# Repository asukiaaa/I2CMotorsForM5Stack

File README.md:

# I2cMotorsForM5Stack

A motor driver with using atmega328p for M5Stack.

# Components

- [TB6612FNG](http://akizukidenshi.com/catalog/g/gI-11317/)
- [Diode](https://akizukidenshi.com/catalog/g/gI-02073/)
- [Terminal block](https://akizukidenshi.com/catalog/g/gP-08370/)
- Gear motor 6v200rpm

# License

MIT

# References

- [SparkFun Motor Driver - Dual TB6612FNG (1A)](https://www.sparkfun.com/products/14451)
- [CavityForM5Stack](https://github.com/asukiaaa/CavityForM5Stack)
- [Arduino Pro Mini schematic (PDF)](https://www.arduino.cc/en/uploads/Main/Arduino-Pro-Mini-schematic.pdf)

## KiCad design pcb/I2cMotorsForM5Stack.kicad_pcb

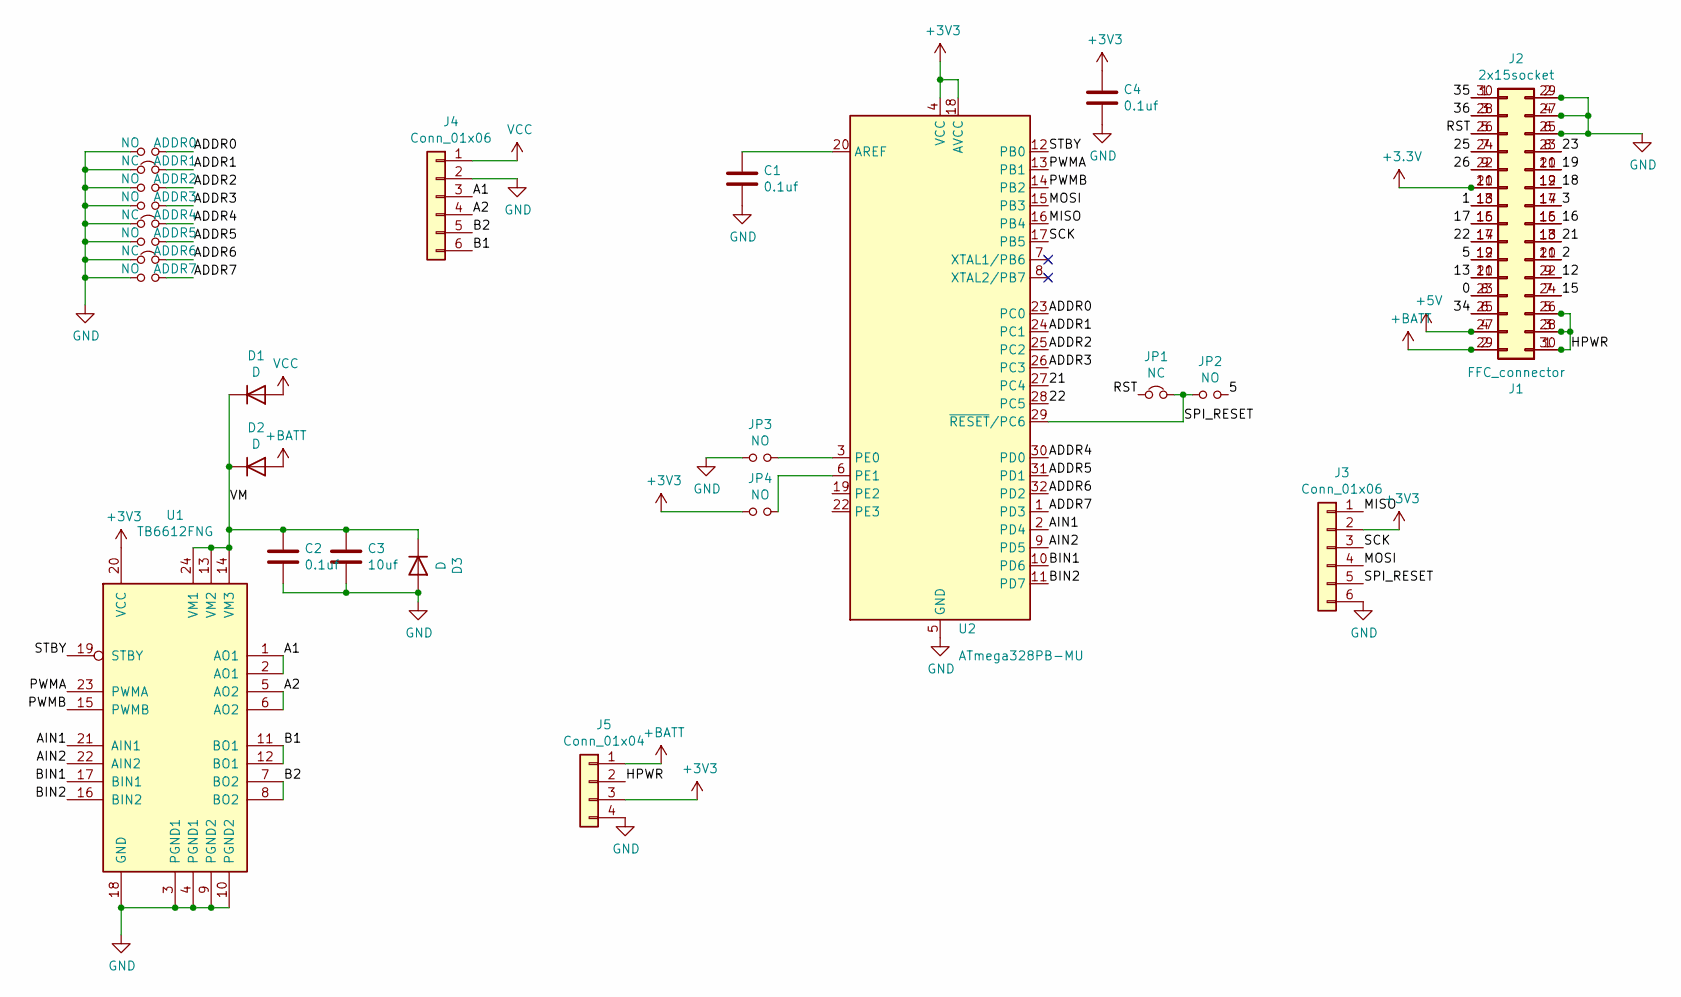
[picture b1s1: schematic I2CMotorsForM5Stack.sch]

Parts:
ADDR0, ADDR2, ADDR3, ADDR5, ADDR7: NO; SolderJumper-2_P1.3mm_Open_RoundedPad1.0x1.5mm
ADDR1, ADDR4, ADDR6: NC; SolderJumper-2_P1.3mm_Bridged_RoundedPad1.0x1.5mm
C1, C2, C4: 0.1uf; C_0603_1608Metric
C3: 10uf; C_0805_2012Metric
D1, D2, D3: D; D_SOD-123F
J1: FFC_connector; Hirose_FH12-30S-0.5SH_1x30-1MP_P0.50mm_Horizontal
J2: 2x15socket; PinSocket_2x15_P2.54mm_Vertical_SMD_just_for_M5Stack_bottom
J3: Conn_01x06; 2x03_P2.54mm_Pads
J4: Conn_01x06; TerminalBlock_bornier-6_P5.08mm
J5: Conn_01x04; NS-Tech_Grove_1x04_P2mm_Vertical
JP1: NC; SolderJumper-2_P1.3mm_Bridged_RoundedPad1.0x1.5mm
JP2, JP3, JP4: NO; SolderJumper-2_P1.3mm_Open_RoundedPad1.0x1.5mm
U1: TB6612FNG; SSOP-24_5.3x8.2mm_P0.65mm
U2: ATmega328PB-MU; QFN-32-1EP_5x5mm_P0.5mm_EP3.1x3.1mm

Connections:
+5V: J1.4, J2.27
+BATT: D2.2 (A), J1.2, J2.29, J5.1
/0: J1.8, J2.23
/1: J1.18, J2.13
/2: J1.11, J2.20
/3: J1.17, J2.14
/5: J1.12, J2.19, JP2.2
/12: J1.9, J2.22
/13: J1.10, J2.21
/15: J1.7, J2.24
/16: J1.15, J2.16
/17: J1.16, J2.15
/18: J1.19, J2.12
/19: J1.21, J2.10
/21: J1.13, J2.18, U2.27 (PC4)
/22: J1.14, J2.17, U2.28 (PC5)
/23: J1.23, J2.8
/25: J1.24, J2.7
/26: J1.22, J2.9
/34: J1.6, J2.25
/35: J1.30, J2.1
/36: J1.28, J2.3
/A1: J4.3, U1.1 (AO1), U1.2 (AO1)
/A2: J4.4, U1.5 (AO2), U1.6 (AO2)
/ADDR0: ADDR0.2, U2.23 (PC0)
/ADDR1: ADDR1.2, U2.24 (PC1)
/ADDR2: ADDR2.2, U2.25 (PC2)
/ADDR3: ADDR3.2, U2.26 (PC3)
/ADDR4: ADDR4.2, U2.30 (PD0)
/ADDR5: ADDR5.2, U2.31 (PD1)
/ADDR6: ADDR6.2, U2.32 (PD2)
/ADDR7: ADDR7.2, U2.1 (PD3)
/AIN1: U1.21 (AIN1), U2.2 (PD4)
/AIN2: U1.22 (AIN2), U2.9 (PD5)
/B1: J4.6, U1.11 (BO1), U1.12 (BO1)
/B2: J4.5, U1.7 (BO2), U1.8 (BO2)
/BIN1: U1.17 (BIN1), U2.10 (PD6)
/BIN2: U1.16 (BIN2), U2.11 (PD7)
/MISO: J3.1, U2.16 (PB4)
/MOSI: J3.4, U2.15 (PB3)
/PWMA: U1.23 (PWMA), U2.13 (PB1)
/PWMB: U1.15 (PWMB), U2.14 (PB2)
/RST: J1.26, J2.5, JP1.1
/SCK: J3.3, U2.17 (PB5)
/SPI_RESET: J3.5, JP1.2, JP2.1, U2.29 (~RESET~/PC6)
/STBY: U1.19 (STBY), U2.12 (PB0)
/VM: C2.1, C3.1, D1.1 (K), D2.1 (K), D3.1 (K), U1.13 (VM2), U1.14 (VM3), U1.24 (VM1)
GND: ADDR0.1, ADDR1.1, ADDR2.1, ADDR3.1, ADDR4.1, ADDR5.1, ADDR6.1, ADDR7.1, C1.2, C2.2, C3.2, C4.2, D3.2 (A), J1.25, J1.27, J1.29, J2.2, J2.4, J2.6, J3.6, J4.2, J5.4, JP3.1, U1.3 (PGND1), U1.4 (PGND1), U1.9 (PGND2), U1.10 (PGND2), U1.18 (GND), U2.5 (GND), U2.21 (GND), U2.33 (GND)
unnamed: C1.1, U2.20 (AREF)
unnamed: JP3.2, U2.3 (PE0)
unnamed: JP4.2, U2.6 (PE1)
VCC: D1.2 (A), J4.1

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
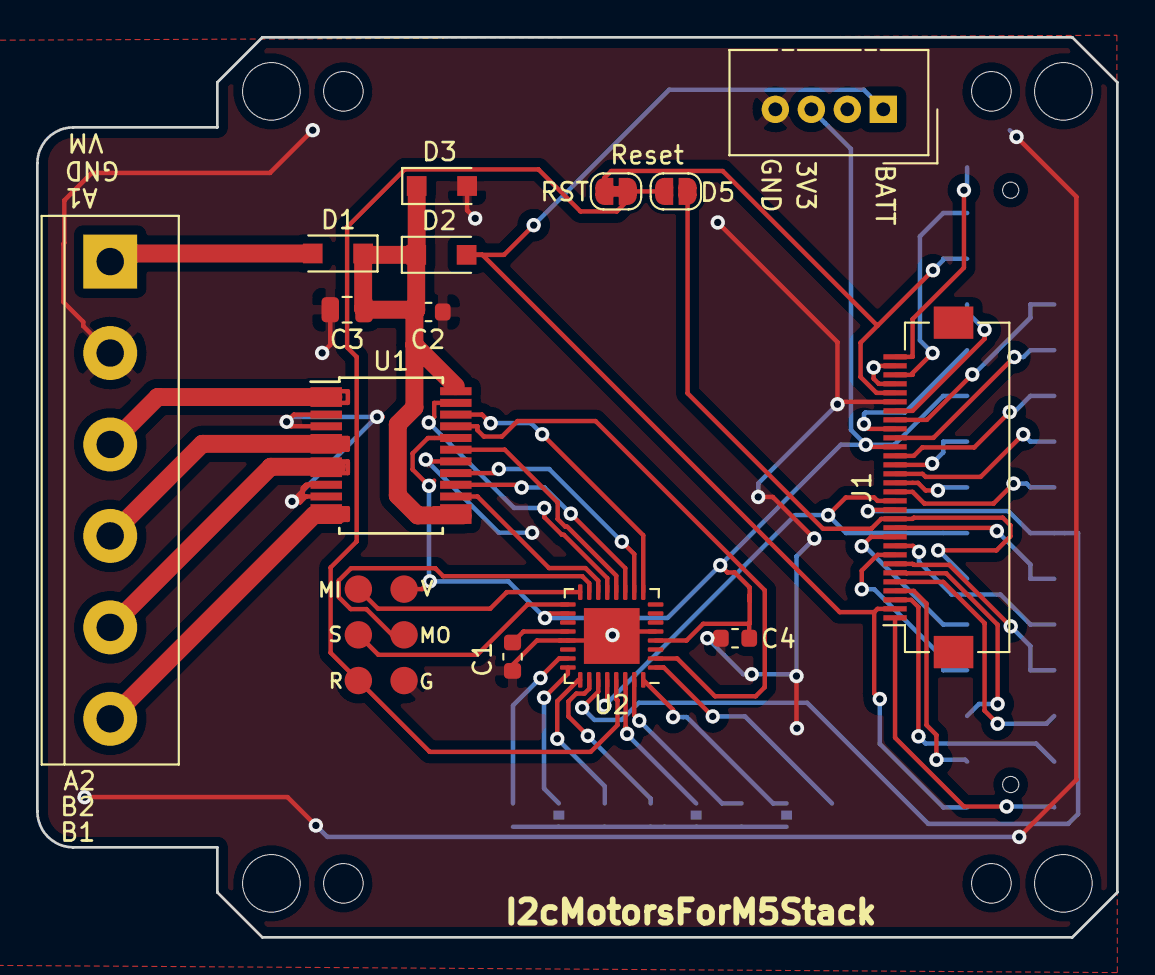
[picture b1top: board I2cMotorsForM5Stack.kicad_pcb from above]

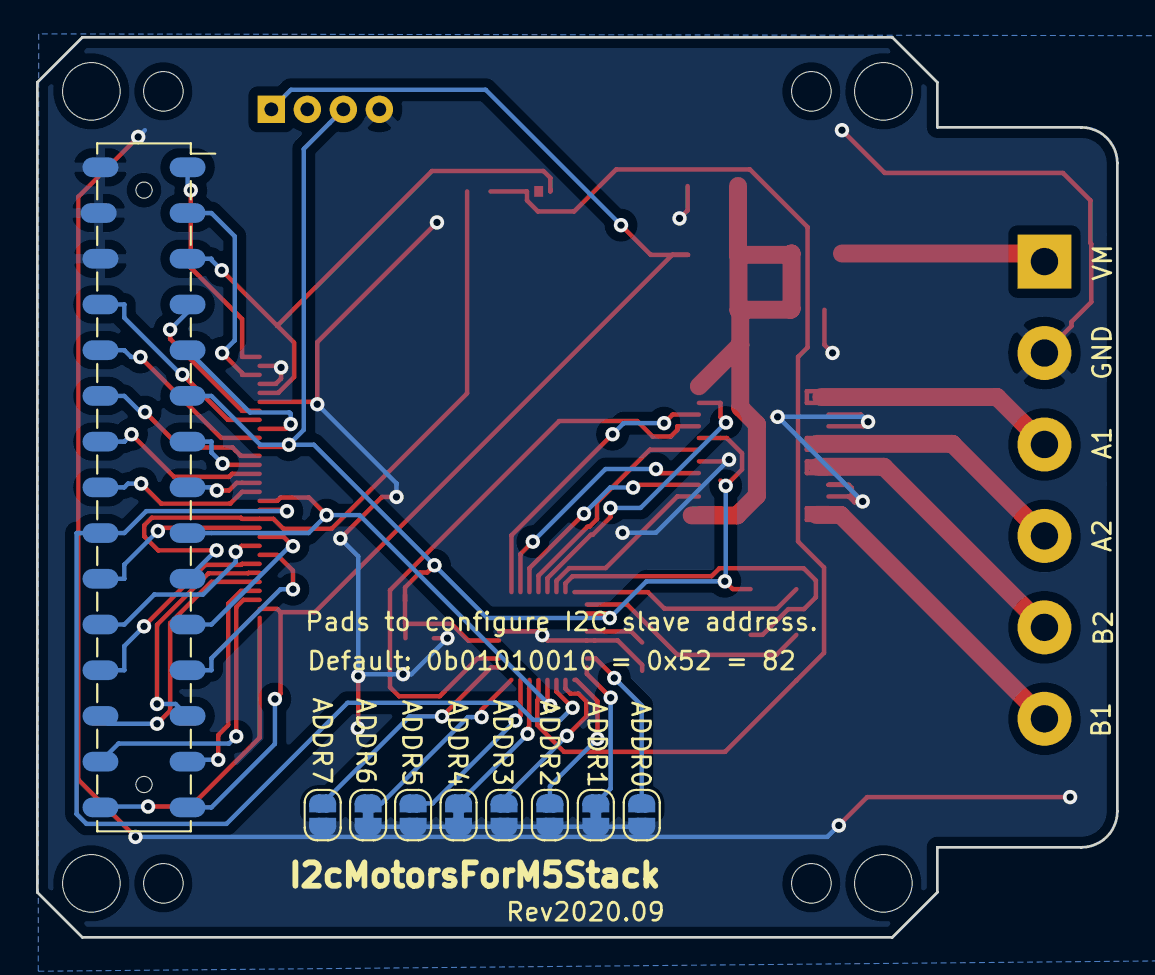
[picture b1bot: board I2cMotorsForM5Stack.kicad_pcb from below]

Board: 2 copper layers, 60.0 x 50.0 mm, 32 parts (9 on the bottom side), 54 nets.

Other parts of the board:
REF1, REF4, REF6, REF9: MountingHole_3.2mm_M3
REF2, REF3, REF7, REF8: MountingHole_2.2mm_M2

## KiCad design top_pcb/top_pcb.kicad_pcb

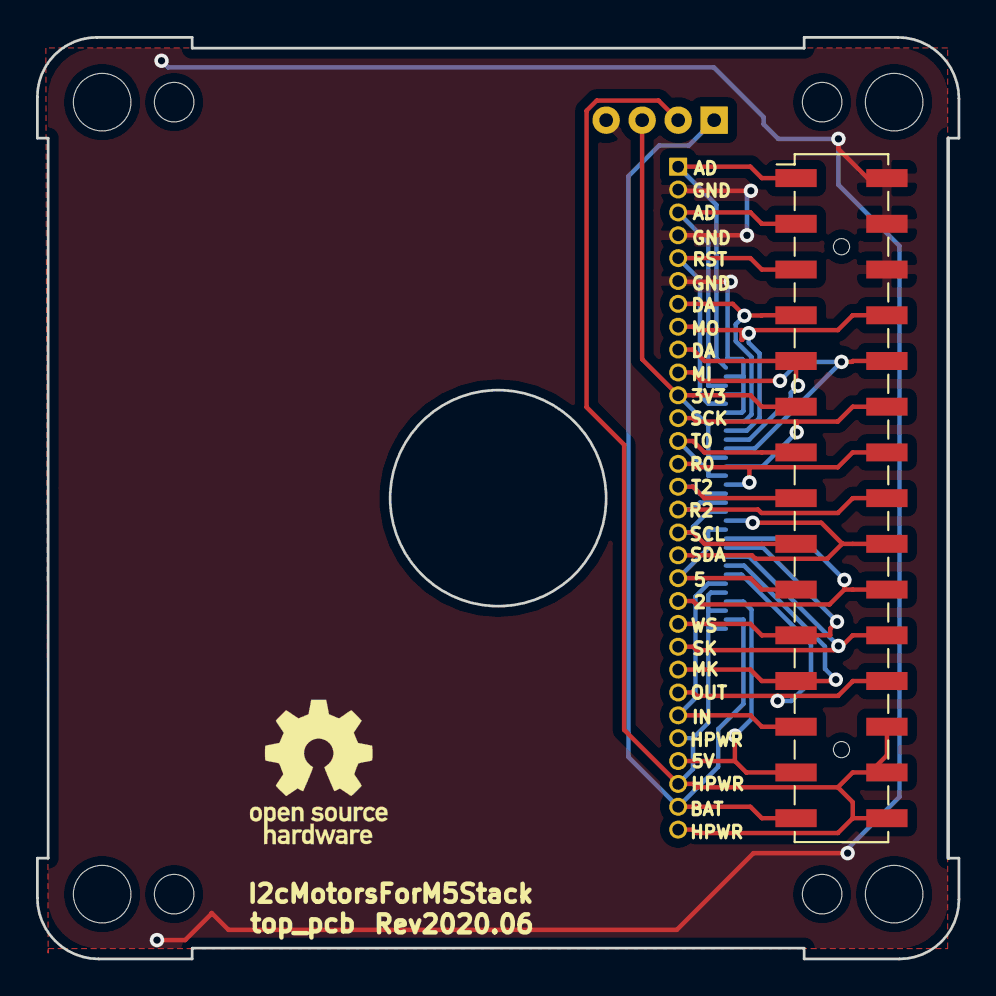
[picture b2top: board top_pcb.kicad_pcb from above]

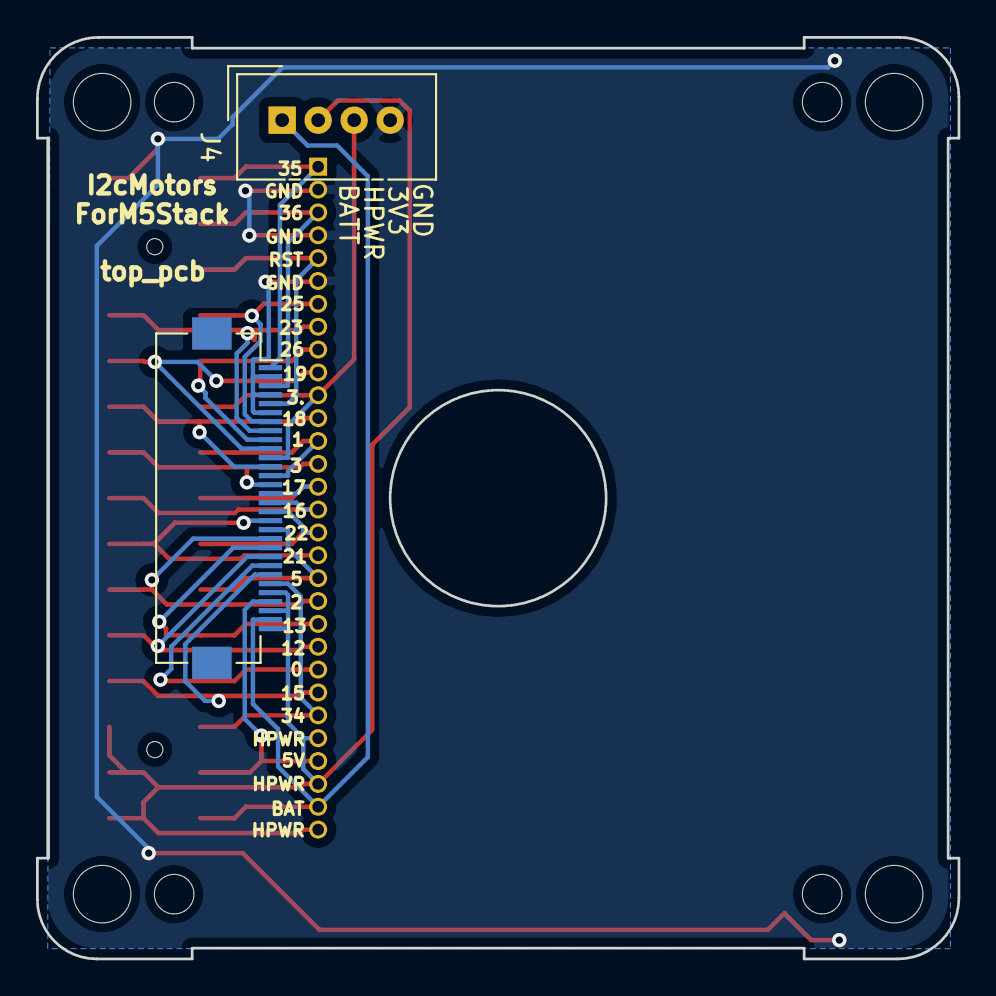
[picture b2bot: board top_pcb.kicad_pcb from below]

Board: 2 copper layers, 51.2 x 51.2 mm, 17 parts (2 on the bottom side), 26 nets.

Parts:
J1: flat_cable_connector; Hirose_FH12-30S-0.5SH_1x30-1MP_P0.50mm_Horizontal
J2: header; PinHeader_2x15_P2.54mm_Vertical_SMD_for_M5Stack
J3: free_holes; PinHeader_1x30_P1.27mm_Vertical_without_silks
J4: Conn_01x04; NS-Tech_Grove_1x04_P2mm_Vertical
OSHWREF2: OSHW-Logo_7.5x8mm_SilkScreen
REF1, REF4, REF6, REF9: MountingHole_3.2mm_M3
REF2, REF3, REF7, REF8: MountingHole_2.2mm_M2
corner1, corner4: corner_edge1
corner2, corner3: corner_edge2

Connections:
+3V3: J1.11, J2.11, J3.11, J4.3
+5V: J1.27, J2.27, J3.27
+BATT: J1.29, J2.29, J3.29, J4.1
G0: J1.23, J2.23, J3.23
G1: J1.13, J2.13, J3.13
G2: J1.20, J2.20, J3.20
G3: J1.14, J2.14, J3.14
G5: J1.19, J2.19, J3.19
G12: J1.22, J2.22, J3.22
G13: J1.21, J2.21, J3.21
G15: J1.24, J2.24, J3.24
G16: J1.16, J2.16, J3.16
G17: J1.15, J2.15, J3.15
G18: J1.12, J2.12, J3.12
G19: J1.10, J2.10, J3.10
G21: J1.18, J2.18, J3.18
G22: J1.17, J2.17, J3.17
G23: J1.8, J2.8, J3.8
G25: J1.7, J2.7, J3.7
G26: J1.9, J2.9, J3.9
G34: J1.25, J2.25, J3.25
G35: J1.1, J2.1, J3.1
G36: J1.3, J2.3, J3.3
GND: J1.2, J1.4, J1.6, J2.2, J2.4, J2.6, J3.2, J3.4, J3.6, J4.4
HPWR: J1.26, J1.28, J1.30, J2.26, J2.28, J2.30, J3.26, J3.28, J3.30, J4.2
RST: J1.5, J2.5, J3.5

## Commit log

2020-02-20 Create pcb folder
2020-02-20 Add plate that uses motor holder
2020-02-22 Update design of plate to use small moter with 2 plates
2020-02-23 Update position of holes for a caster
2020-02-23 Add holes to horizontal mount for M5Stack
2020-03-02 Update outer size of plate
2020-03-09 Put terminal mount out side of m5stack zone
2020-03-10 Remove redundant files
2020-03-10 Add gerber_to_order to gitignore
2020-03-10 Use rounded corner
2020-03-30 Add diode to connect VM and GND
2020-03-30 Assign thick line to motor power
2020-03-30 Add connectors and address pads
2020-04-07 Update plate to use hole castor
2020-05-02 Change start number for address pad
2020-05-02 Correct accidentaly connected line
2020-05-02 Add connector to support power lines
2020-05-02 Add components info
2020-05-02 Add top_pcb
2020-05-02 Rename project to I2cMotorsForM5Stack
2020-05-02 Add explanation about pads to configure address
2020-06-28 Update something
2020-06-28 Ignore gerber_to_order for top_pcb
2020-06-28 Remove accidentaly connected gnd line to battery pad
2020-06-28 Add schema pdf
2020-06-28 Update rpm for gear motor
2020-09-04 Separate HPWR to NC0-2 for Core2
2020-09-19 Update list of components on readme
2020-11-08 Update pdf of schematic
2020-11-08 Add .zip to .gitignore
